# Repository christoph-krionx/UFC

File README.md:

# UFC – configurable MIDI foot controller

A MIDI foot controller for guitarists, built around an Arduino Mega 2560 Pro.
Every switch can send program changes and control changes to amps, modellers and effects.
The assignment is edited on the device itself or with a web editor over USB.

The same board and firmware are used in two builds:

| Variant | `BOARD` | Switches | LEDs | Display | Pages |
| --- | --- | --- | --- | --- | --- |
| UFC | `1` (default) | 21 foot switches, 4 external switches | 2 per switch | 20x2 LCD with edit mode | 1 |
| Stomp6 | `2` | 6 foot switches | 1 per switch | 20x2 LCD with the switch names, configured with the web editor | 2 (scenes, pedalboard) |

## Hardware

Board **UFC rev. 1** (KiCad 10 project in `hardware/UFC`, schematic as [PDF](hardware/UFC/UFC.pdf)):

- RobotDyn Mega 2560 Pro (ATmega2560, CH340 USB serial)
- 21 foot switches in four rows (3 + 6 + 6 + 6), each with two WS2812 LEDs
- 4 inputs for external switches, 2 inputs for expression pedals
- 20x2 character LCD (HD44780)
- 2 MIDI inputs and 2 MIDI outputs (5 pin DIN)

### Board revisions

| Revision | Date | Git tag | Notes |
| --- | --- | --- | --- |
| rev. 1 | 2026-10-12 | `hw-rev1` | LCD pin 5 (R/W) connected to GND |
| rev. 0 | 2018-10-05 | `hw-rev0` | manufactured, has a known error (see below) |

**Known error of rev. 0:** pin 5 (R/W) of the LCD is connected to +5 V instead of GND.
The display stays in read mode and shows nothing.
Rework for existing boards: cut the connection between pin 5 and +5 V at the display connector and connect pin 5 to GND, for example to pin 1.

The firmware runs on both revisions without changes.
The fabrication files of rev. 1 are in `hardware/UFC/Gerber`, those of rev. 0 in `hardware/UFC/Gerber/rev00`.

### Pin assignment

The firmware takes the mapping from `firmware/ufc/Board.h`.

| Function | Arduino pin | Connector | Notes |
| --- | --- | --- | --- |
| LCD RS / EN | D5 / D7 | DISP1 | 4 bit mode, R/W tied to GND (rev. 0: see board revisions) |
| LCD DB4 – DB7 | D9, D11, D13, D15 | DISP1 | contrast set with trimmer RV1 |
| LED data | D6 | J22 | WS2812 chain, 220 Ω in series |
| LED power enable | D12 | – | active low, switches the LED supply |
| MIDI 1 out / in | D18 (TX1) / D19 (RX1) | J23 / J25 | `Serial1`, input with optocoupler |
| MIDI 2 out / in | D16 (TX2) / D17 (RX2) | J24 / J26 | `Serial2`, input with optocoupler |
| Expression pedal 1 / 2 | A0 / A1 | J27 / J28 | AREF is driven externally, the firmware has to use `analogReference(EXTERNAL)` |
| External switch 1 / 2 | D21 / D22 | J29 | active low |
| External switch 3 / 4 | D23 / D24 | J30 | active low |
| USB serial (editor, upload) | D0 / D1 | USB | CH340 on the Mega 2560 Pro |
| Supply | VIN / 5V | J32 / J31 | |

Unused pins: D2, D3, D4, D8, D10, D14, D20, D25 – D32, A2 – A15.

### Foot switches and LEDs

The switches are numbered from bottom left to top right as seen by the player.
All switch inputs are active low with a 10 kΩ pull-up and 100 nF on the board.
The LED chain starts at switch 19 and snakes down row by row, the table shows the position of the left and right LED in the chain (0 – 41).

| Row | Switch | Arduino pin | Connector | LED left / right |
| --- | --- | --- | --- | --- |
| 4 (top) | 19 | D51 | J1 | 0 / 1 |
| | 20 | D49 | J2 | 2 / 3 |
| | 21 | D45 | J3 | 4 / 5 |
| 3 | 13 | D40 | J9 | 17 / 16 |
| | 14 | D37 | J8 | 15 / 14 |
| | 15 | D35 | J7 | 13 / 12 |
| | 16 | D33 | J6 | 11 / 10 |
| | 17 | D41 | J5 | 9 / 8 |
| | 18 | D44 | J4 | 7 / 6 |
| 2 | 7 | D39 | J10 | 18 / 19 |
| | 8 | D52 | J11 | 20 / 21 |
| | 9 | D50 | J12 | 22 / 23 |
| | 10 | D48 | J13 | 24 / 25 |
| | 11 | D47 | J14 | 26 / 27 |
| | 12 | D42 | J15 | 28 / 29 |
| 1 (bottom) | 1 | D53 | J21 | 41 / 40 |
| | 2 | D46 | J20 | 39 / 38 |
| | 3 | D43 | J19 | 37 / 36 |
| | 4 | D38 | J18 | 35 / 34 |
| | 5 | D36 | J17 | 33 / 32 |
| | 6 | D34 | J16 | 31 / 30 |

### Stomp6 variant

Six foot switches in two rows of three, one WS2812 LED per switch.
The 20x2 LCD (Fordata FC2002C, same connection as on the UFC) sits between the rows.
MIDI 1 has input and output, MIDI 2 only the output.
The mapping is in `firmware/ufc/Board_Stomp6.h`.
The LED chain starts at switch 3 (bottom right), runs to the left and back through the top row.

| Row | Switch | Arduino pin | Connector | LED |
| --- | --- | --- | --- | --- |
| top | 4 | D35 | J7 | 3 |
| | 5 | D33 | J6 | 4 |
| | 6 | D41 | J5 | 5 |
| bottom | 1 | D44 | J4 | 2 |
| | 2 | D45 | J3 | 1 |
| | 3 | D49 | J2 | 0 |

## Repository

| Folder | Content |
| --- | --- |
| `firmware/ufc` | controller firmware |
| `firmware/ufc_hwtest` | stand-alone hardware test |
| `editor` | web editor (plain HTML and JavaScript, no build step) |
| `hardware/UFC` | schematic, layout, project libraries and Gerber files |

## Firmware

Features of the current version:

- 8 presets with names, the last used preset is restored after power on
- up to 3 messages per switch (Stomp6: 5), program change or control change, each with MIDI output and channel
- switch modes: toggle, momentary and group (only one switch of the group on the same page is active)
- global switches which keep their function in every preset, for example preset up / down or tuner; on boards with pages a switch is global per page (Stomp6: a global pedalboard block, the scene at the same place stays per preset)
- messages which are sent when a preset is loaded
- pages: every preset has its own switch assignment per page (Stomp6: page 1 scenes, page 2 pedalboard)
- links: a switch sets the switches of the last page on or off when it is switched on, the LEDs follow (Stomp6: a scene sets the pedalboard blocks)
- actions: long press of a switch or two switches pressed together, for example tuner, preset up / down or page change; a switch with an action reacts on release
- Stomp6 display: line 1 shows the names of the top row, line 2 the names of the bottom row, each name above / below its switch; the names follow the page.
  Preset number, name and tempo, the page name and the tap tempo are shown in line 1 for 1.5 s, the name of an active MIDI action (for example `TUNER`) replaces line 1 while the action is on
  If the top left and the top middle switch have no function or no name, line 1 keeps showing preset number and name (with the tempo if the top right switch is free too)
- optional pause after a program change, optionally a program change is only sent if it differs from the last one on the channel
- MIDI clock with a tempo per preset (0: no clock until tapped), tap tempo on a switch with the function "Tap" or on the active group switch pressed again, the tap switch flashes in time
- configuration stored in the internal EEPROM, every block protected by a checksum; a configuration of the other variant or an older format is replaced by the factory configuration

### Build and upload

The firmware is a plain Arduino sketch. Required libraries: FastLED and LiquidCrystal.

```bash
arduino-cli compile --fqbn arduino:avr:mega firmware/ufc
```

```bash
arduino-cli upload --fqbn arduino:avr:mega -p <port> firmware/ufc
```

The Stomp6 variant is selected with `BOARD=2`, compile and upload in one step:

```bash
arduino-cli compile --fqbn arduino:avr:mega --build-property "build.extra_flags=-DBOARD=2" --upload -p <port> firmware/ufc
```

The Arduino IDE works as well: open `firmware/ufc/ufc.ino` and select the board "Arduino Mega or Mega 2560".
For the Stomp6 variant change the default of `BOARD` in `firmware/ufc/Board.h`.

### Stomp6 with a Sonulab StompStation PRO

The factory configuration of the Stomp6 variant is made for the StompStation PRO on MIDI channel 1 (StompStation: Setting, Misc, MIDI Address 0).
The StompStation has a 3.5 mm TRS jack, the MIDI cable needs a **Type A** adapter.

| Gesture | Function |
| --- | --- |
| switch 1 – 6 | scene (page 1) or block on / off (page 2) |
| active scene again | tap tempo, the scene flashes in time while the MIDI clock runs |
| hold switch 1 | tuner on / off (CC 11), switch 1 lights red while it is on |
| hold switch 6 | change between scenes and pedalboard |
| switch 1 + 2 | previous preset |
| switch 2 + 3 | next preset |

All presets are empty, the scenes are assigned in the editor.
The pedalboard is global with Drive (CC 1), Comp (CC 8), Wah (CC 14), Mod post (CC 6), Delay (CC 10) and Reverb (CC 5).
The actions above and tap tempo on the active scene are part of the factory configuration.
Delay and modulation of the StompStation follow the MIDI clock if they are locked to the global tempo.

A setup used with the StompStation: presets 1 – 6 are one main sound each, the start message of the preset sends PC 0 – 5.
The scenes (for example rhythm, solo, clean) send the same program change and set all six pedalboard blocks, so the LEDs always show the real state.
Useful fixed control changes of the StompStation:

| CC | Block | CC | Block |
| --- | --- | --- | --- |
| 1 | Drive | 9 | Gate |
| 2 | Mod pre | 10 | Delay 1 |
| 3 | Amp | 11 | Tuner |
| 4 | IR | 12 | Expr |
| 5 | Reverb | 13 | Expr Boost |
| 6 | Mod post | 14 | Wah |
| 7 | Tremolo | 15 | EQ |
| 8 | Comp | 16 | Pitch |

Values 0 – 63 switch a block off, 64 – 127 on. CC 20 is the global volume, CC 21 / 22 select the next / previous preset.
Other parameters are reached with the assignable controllers 1 – 3 of the StompStation (CC 32 – 127).

Tested behaviour of the StompStation (firmware of October 2026):

- a program change switches presets without asking, unsaved changes of the active preset are discarded
- a control change sent directly after a program change is applied
- the program change of the active preset loads it again, switching within a bank of three is gapless
- CC 21 / 22 select the next / previous preset (the troubleshooting chapter of the manual names CC 12 / 13 by mistake)
- the StompStation sends no state, the controller cannot know changes made on the pedal itself

### Edit mode on the device

Hold switch 19 and 20 (top row) for one second. The bottom row then works as keys:

| Switch | Function |
| --- | --- |
| 1 / 2 | previous / next field |
| 3 / 4 | value down / up, hold to repeat |
| 5 | back, unsaved changes are discarded |
| 6 | save |

Stepping on any other switch selects it for editing.

Holding switch 19 and 21 during power on restores the factory configuration (Stomp6: switch 4 and 6).
The Stomp6 variant has no edit mode.

## Web editor

The editor talks to the controller with the Web Serial API and therefore needs Chrome or Edge on a desktop computer.

```bash
python -m http.server 8137 --bind 127.0.0.1 --directory editor
```

Open `http://localhost:8137`, connect and select the serial port of the controller.
The configuration can also be saved to and loaded from a file.
The editor adapts to the connected variant, pages are selected above the switches, actions and the program change options are under "Global".
Files of older firmware versions (0.3 and later) can be loaded: values the file does not have are taken from the connected device or set to defaults, a switch that was global keeps its global definition on every page, actions get an empty name.
A file of the other variant (different number of switches) is rejected.

The serial protocol is described in `firmware/ufc/Protocol.h`, the data format in `firmware/ufc/Config.h` and `firmware/ufc/Storage.h`.

## Hardware test

`firmware/ufc_hwtest` checks display, LEDs, switches and both MIDI ports and shows the result on the display.
The MIDI test needs a DIN cable from each output to an input.

## License

MIT, see [LICENSE](LICENSE).

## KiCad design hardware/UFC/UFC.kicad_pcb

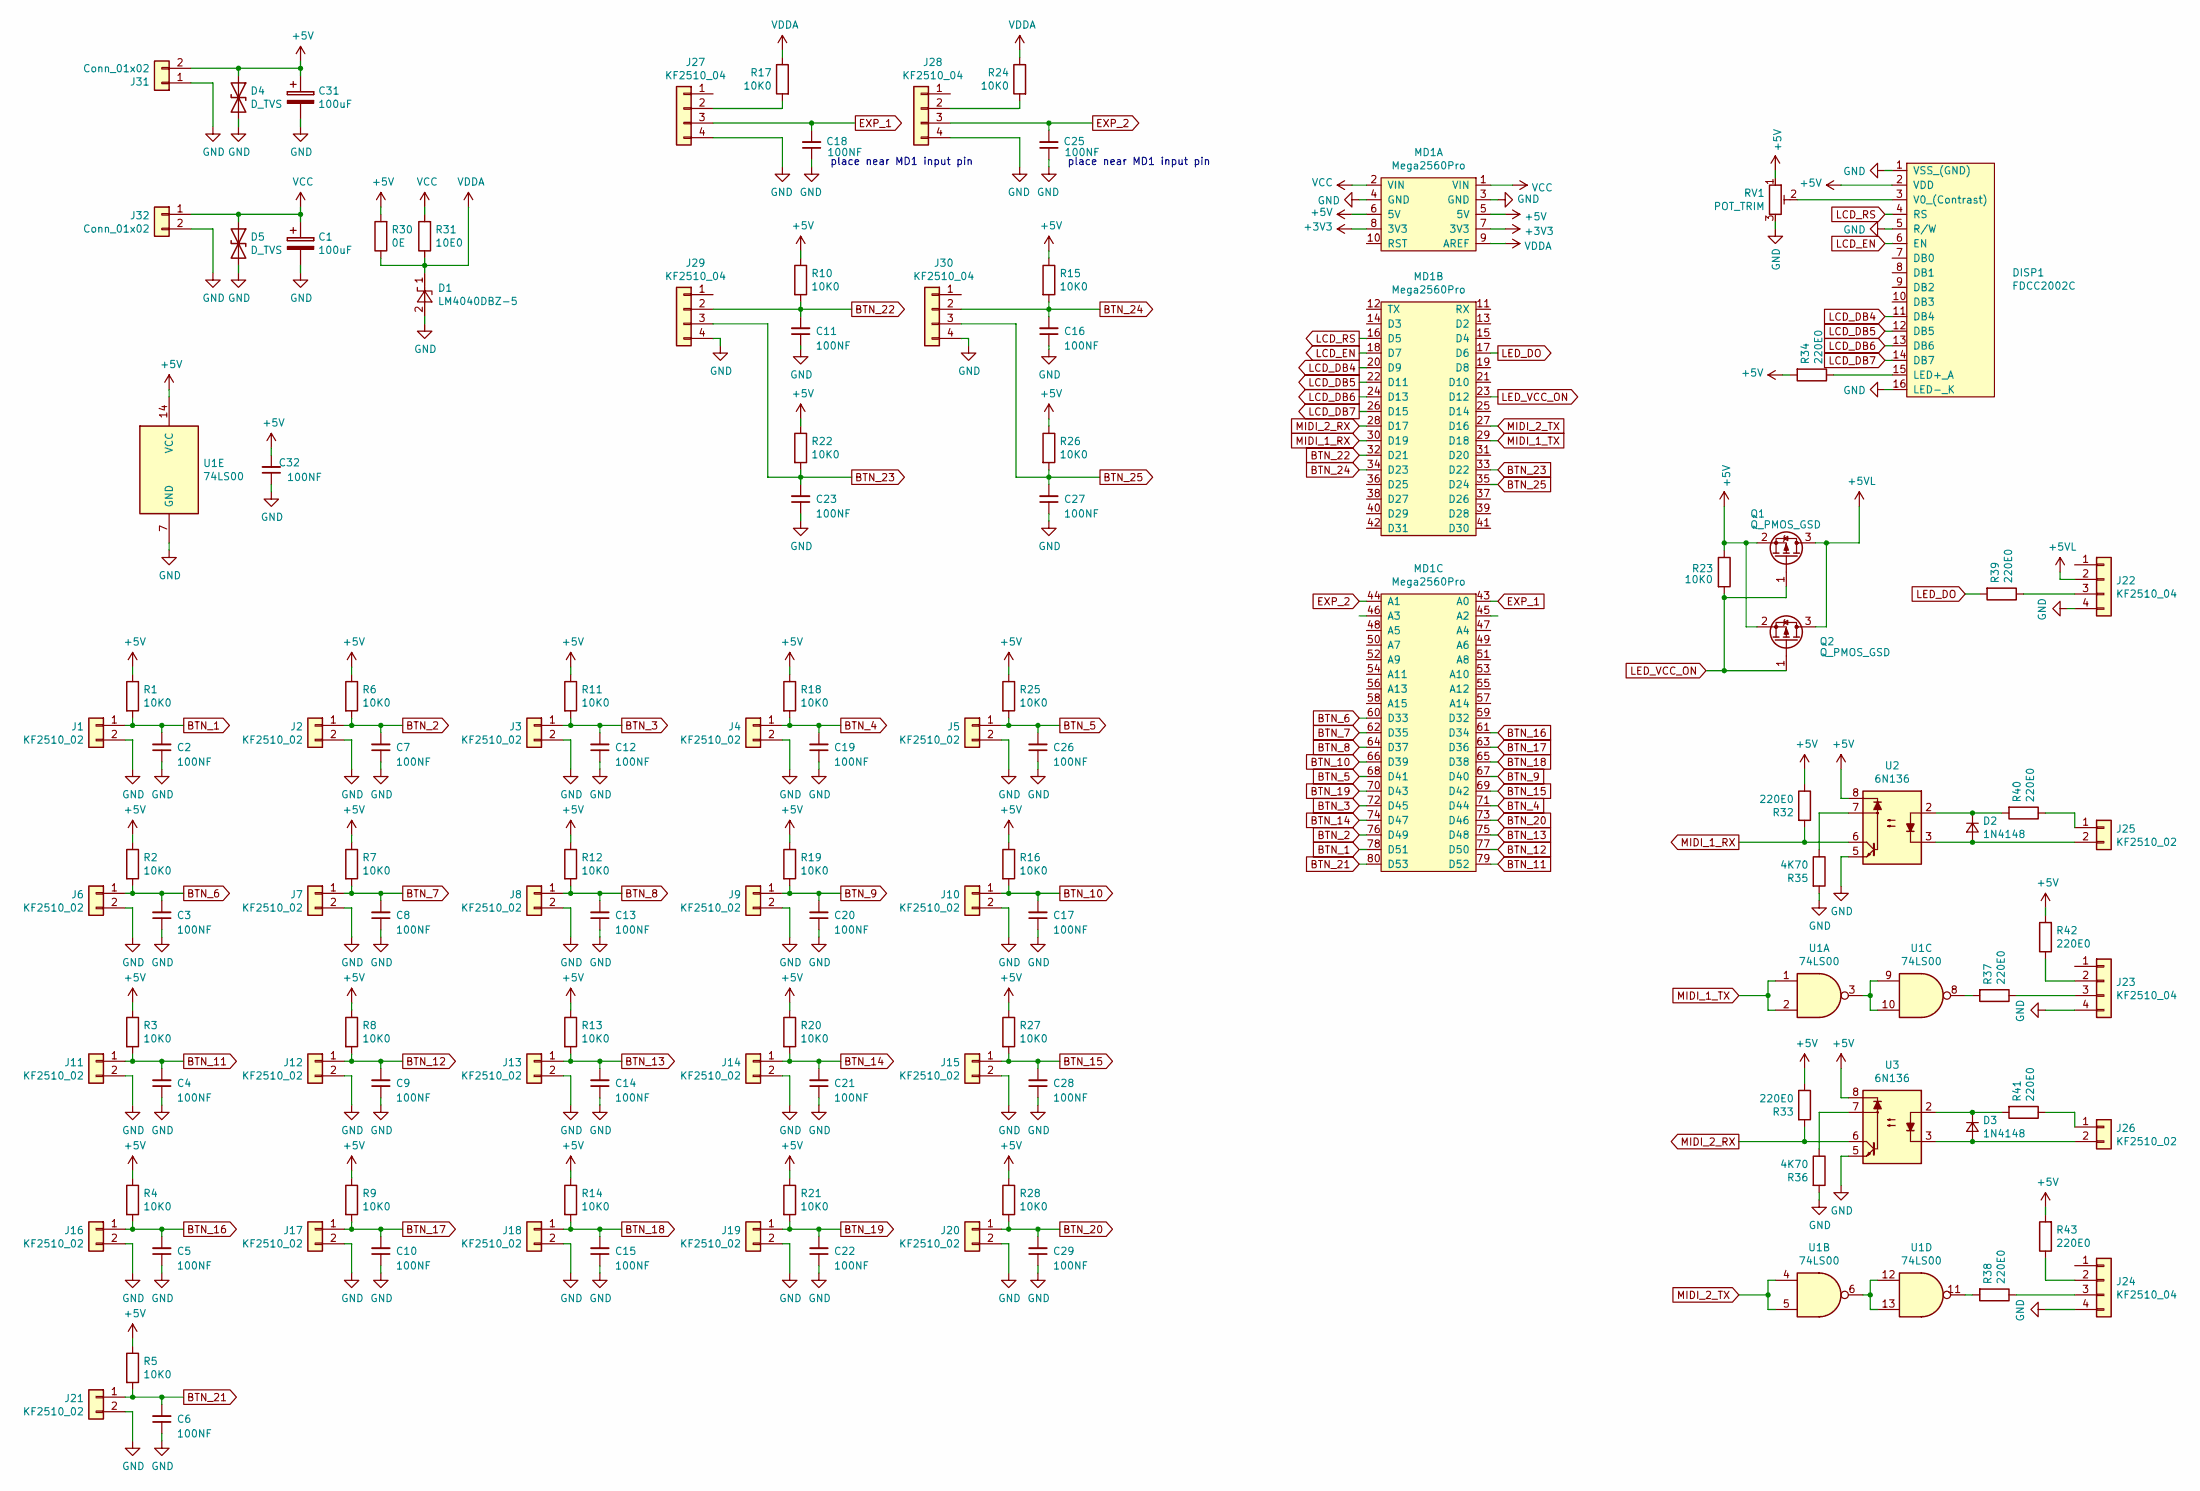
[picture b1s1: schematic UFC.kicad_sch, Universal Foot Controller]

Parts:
C1, C31: 100uF; CP_Radial_D10.0mm_P5.00mm
C2, C3, C4, C5, C6, C7, C8, C9, C10, C11, C12, C13, C14, C15, C16, C17, C18, C19, C20, C21, C22, C23, C25, C26, C27, C28, C29, C32: 100NF; C_0805_2012Metric_Pad1.29x1.40mm_HandSolder
D1: LM4040DBZ-5; SOT-23
D2, D3: 1N4148; D_DO-41_SOD81_P7.62mm_Horizontal
D4, D5: D_TVS; D_SMA_Handsoldering
DISP1: FDCC2002C
J1, J2, J3, J4, J5, J6, J7, J8, J9, J10, J11, J12, J13, J14, J15, J16, J17, J18, J19, J20, J21, J25, J26: KF2510_02; Molex_KK-254_AE-6410-02A_1x02_P2.54mm_Vertical
J22, J23, J24, J27, J28, J29, J30: KF2510_04; Molex_KK-254_AE-6410-04A_1x04_P2.54mm_Vertical
J31, J32: Conn_01x02; TerminalBlock_Phoenix_PT-1,5-2-3.5-H_1x02_P3.50mm_Horizontal
MD1: Mega2560Pro; Mega2560Core
Q1, Q2: Q_PMOS_GSD; SOT-23_Handsoldering
R1, R2, R3, R4, R5, R6, R7, R8, R9, R10, R11, R12, R13, R14, R15, R16, R17, R18, R19, R20, R21, R22, R23, R24, R25, R26, R27, R28: 10K0; R_0805_2012Metric_Pad1.29x1.40mm_HandSolder
R30: 0E; R_0805_2012Metric_Pad1.29x1.40mm_HandSolder
R31: 10E0; R_0805_2012Metric_Pad1.29x1.40mm_HandSolder
R32, R33, R37, R38, R39, R40, R41, R42, R43: 220E0; R_0805_2012Metric_Pad1.29x1.40mm_HandSolder
R34: 220E0; R_1206_3216Metric_Pad1.39x1.80mm_HandSolder
R35, R36: 4K70; R_0805_2012Metric_Pad1.29x1.40mm_HandSolder
RV1: POT_TRIM; Potentiometer_Trimmer_Vishay_TS53YJ
U1: 74LS00; DIP-14_W7.62mm
U2, U3: 6N136; SMD-8

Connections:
+3V3: MD1.7 (3V3), MD1.8 (3V3)
+5V: C31.1, C32.2, D4.1 (A1), DISP1.2 (VDD), J31.2, MD1.5 (5V), MD1.6 (5V), Q1.2 (S), Q2.2 (S), R1.1, R2.1, R3.1, R4.1, R5.1, R6.1, R7.1, R8.1, R9.1, R10.1, R11.1, R12.1, R13.1, R14.1, R15.1, R16.1, R18.1, R19.1, R20.1, R21.1, R22.1, R23.1, R25.1, R26.1, R27.1, R28.1, R30.2, R32.1, R33.1, R34.2, R42.2, R43.2, RV1.1, U1.14 (VCC), U2.8, U3.8
+5VL: J22.2, Q1.3 (D), Q2.3 (D)
BTN_1: C2.2, J1.1, MD1.78 (D51), R1.2
BTN_2: C7.2, J2.1, MD1.76 (D49), R6.2
BTN_3: C12.2, J3.1, MD1.72 (D45), R11.2
BTN_4: C19.2, J4.1, MD1.71 (D44), R18.2
BTN_5: C26.2, J5.1, MD1.68 (D41), R25.2
BTN_6: C3.2, J6.1, MD1.60 (D33), R2.2
BTN_7: C8.2, J7.1, MD1.62 (D35), R7.2
BTN_8: C13.2, J8.1, MD1.64 (D37), R12.2
BTN_9: C20.2, J9.1, MD1.67 (D40), R19.2
BTN_10: C17.2, J10.1, MD1.66 (D39), R16.2
BTN_11: C4.2, J11.1, MD1.79 (D52), R3.2
BTN_12: C9.2, J12.1, MD1.77 (D50), R8.2
BTN_13: C14.2, J13.1, MD1.75 (D48), R13.2
BTN_14: C21.2, J14.1, MD1.74 (D47), R20.2
BTN_15: C28.2, J15.1, MD1.69 (D42), R27.2
BTN_16: C5.2, J16.1, MD1.61 (D34), R4.2
BTN_17: C10.2, J17.1, MD1.63 (D36), R9.2
BTN_18: C15.2, J18.1, MD1.65 (D38), R14.2
BTN_19: C22.2, J19.1, MD1.70 (D43), R21.2
BTN_20: C29.2, J20.1, MD1.73 (D46), R28.2
BTN_21: C6.2, J21.1, MD1.80 (D53), R5.2
BTN_22: C11.2, J29.2, MD1.32 (D21), R10.2
BTN_23: C23.2, J29.3, MD1.33 (D22), R22.2
BTN_24: C16.2, J30.2, MD1.34 (D23), R15.2
BTN_25: C27.2, J30.3, MD1.35 (D24), R26.2
EXP_1: C18.2, J27.3, MD1.43 (A0)
EXP_2: C25.2, J28.3, MD1.44 (A1)
GND: C1.2, C2.1, C3.1, C4.1, C5.1, C6.1, C7.1, C8.1, C9.1, C10.1, C11.1, C12.1, C13.1, C14.1, C15.1, C16.1, C17.1, C18.1, C19.1, C20.1, C21.1, C22.1, C23.1, C25.1, C26.1, C27.1, C28.1, C29.1, C31.2, C32.1, D1.2 (A), D4.2 (A2), D5.2 (A2), DISP1.1 (VSS_(GND)), DISP1.5 (R/W), DISP1.16 (LED-_K), J1.2, J2.2, J3.2, J4.2, J5.2, J6.2, J7.2, J8.2, J9.2, J10.2, J11.2, J12.2, J13.2, J14.2, J15.2, J16.2, J17.2, J18.2, J19.2, J20.2, J21.2, J22.4, J23.4, J24.4, J27.4, J28.4, J29.4, J30.4, J31.1, J32.2, MD1.3 (GND), MD1.4 (GND), R35.2, R36.2, RV1.3, U1.7 (GND), U2.5, U3.5
LCD_DB4: DISP1.11 (DB4), MD1.20 (D9)
LCD_DB5: DISP1.12 (DB5), MD1.22 (D11)
LCD_DB6: DISP1.13 (DB6), MD1.24 (D13)
LCD_DB7: DISP1.14 (DB7), MD1.26 (D15)
LCD_EN: DISP1.6 (EN), MD1.18 (D7)
LCD_RS: DISP1.4 (RS), MD1.16 (D5)
LED_DO: MD1.17 (D6), R39.2
LED_VCC_ON: MD1.23 (D12), Q1.1 (G), Q2.1 (G), R23.2
MIDI_1_RX: MD1.30 (D19), R32.2, U2.6
MIDI_1_TX: MD1.29 (D18), U1.1, U1.2
MIDI_2_RX: MD1.28 (D17), R33.2, U3.6
MIDI_2_TX: MD1.27 (D16), U1.4, U1.5
unnamed: D2.2 (A), J25.2, U2.3
unnamed: D2.1 (K), R40.2, U2.2
unnamed: D3.2 (A), J26.2, U3.3
unnamed: D3.1 (K), R41.2, U3.2
unnamed: DISP1.15 (LED+_A), R34.1
unnamed: DISP1.3 (V0_(Contrast)), RV1.2
unnamed: J22.3, R39.1
unnamed: J23.2, R42.1
unnamed: J23.3, R37.1
unnamed: J24.2, R43.1
unnamed: J24.3, R38.1
unnamed: J25.1, R40.1
unnamed: J26.1, R41.1
unnamed: J27.2, R17.2
unnamed: J28.2, R24.2
unnamed: R35.1, U2.7
unnamed: R36.1, U3.7
unnamed: R37.2, U1.8
unnamed: R38.2, U1.11
unnamed: U1.3, U1.9, U1.10
unnamed: U1.6, U1.12, U1.13
VCC: C1.1, D5.1 (A1), J32.1, MD1.1 (VIN), MD1.2 (VIN), R31.2
VDDA: D1.1 (K), MD1.9 (AREF), R17.1, R24.1, R30.1, R31.1

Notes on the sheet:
place near MD1 input pin

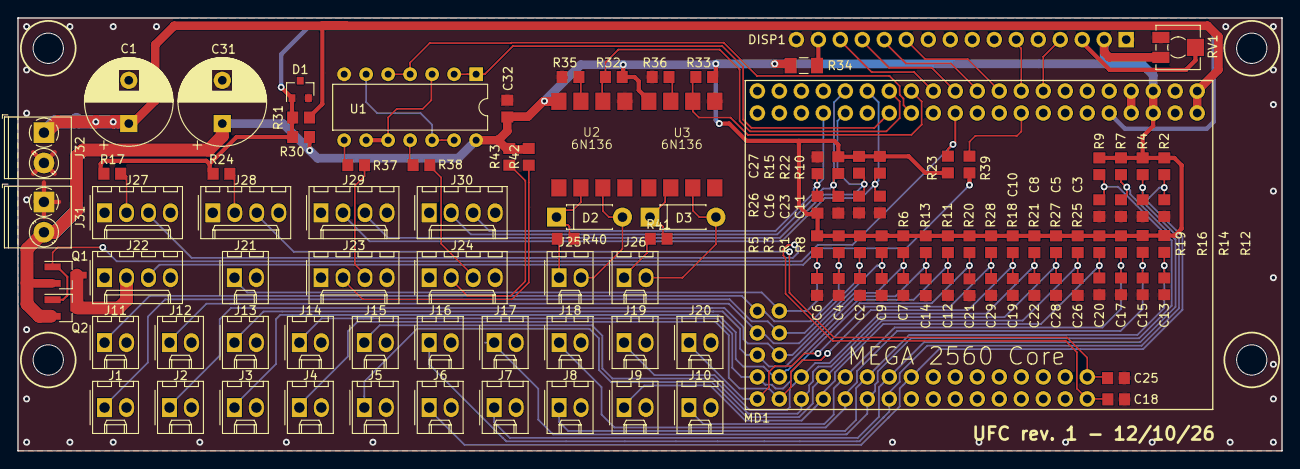
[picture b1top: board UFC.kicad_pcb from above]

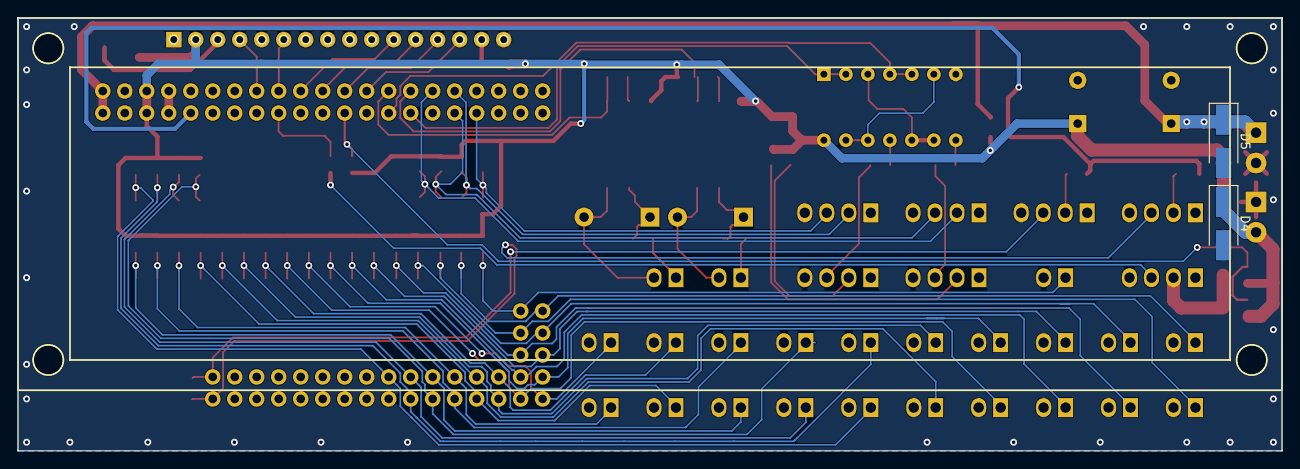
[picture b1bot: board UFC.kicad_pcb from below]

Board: 2 copper layers, 146.0 x 50.0 mm, 117 parts (2 on the bottom side), 66 nets.

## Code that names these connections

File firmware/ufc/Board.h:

/*
	Board definition for the UFC board (hardware/UFC) with a RobotDyn Mega2560 Pro.
	Pin mapping taken from the schematic netlist.

	The same board is used in several builds, select the variant with -DBOARD=<n>
	(arduino-cli: --build-property "build.extra_flags=-DBOARD=2") or by changing the default below.
*/

#ifndef board_h
#define board_h

#include <Arduino.h>

#define BOARD_UFC21	1	// 21 foot switches with two leds each, 4 external switches, lcd
#define BOARD_STOMP6	2	// 6 foot switches with one led each, lcd

#ifndef BOARD
#define BOARD	BOARD_UFC21
#endif

// led power on / off switch (active low)
#define PIN_LED_VCC_ON	12

// WS2812 chain
#define PIN_LED_DATA	6
#define LED_COLOR_ORDER	RGB
#define NO_LED	0xFF

// lcd FDCC2002C / FC2002C (20x2, HD44780, 4 bit mode, r/w tied to gnd), only used if the board has HAS_DISPLAY
#define PIN_LCD_RS	5
#define PIN_LCD_EN	7
#define PIN_LCD_DB4	9
#define PIN_LCD_DB5	11
#define PIN_LCD_DB6	13
#define PIN_LCD_DB7	15
#define LCD_COLS	20
#define LCD_ROWS	2

// expression pedals, AREF is driven externally (VDDA) -> analogReference(EXTERNAL) is mandatory
#define PIN_EXP_1	A0
#define PIN_EXP_2	A1

// midi 1: J25 in / J23 out, midi 2: J26 in / J24 out
// the loopback test showed out 1 -> in 2 and out 2 -> in 1, check the rx assignment before using the inputs
#define MIDI_PORT_1	Serial1
#define MIDI_PORT_2	Serial2
#define MIDI_BAUDRATE	31250

struct SwitchDef
{
	uint8_t pin;
	uint8_t ledLeft;
	uint8_t ledRight;	// NO_LED: the switch has a single led
};

#if BOARD == BOARD_UFC21
#include "Board_UFC21.h"
#elif BOARD == BOARD_STOMP6
#include "Board_Stomp6.h"
#else
#error "unknown board variant"
#endif

#define NUM_SWITCHES	(NUM_FOOT_SWITCHES + NUM_EXT_SWITCHES)

#endif
